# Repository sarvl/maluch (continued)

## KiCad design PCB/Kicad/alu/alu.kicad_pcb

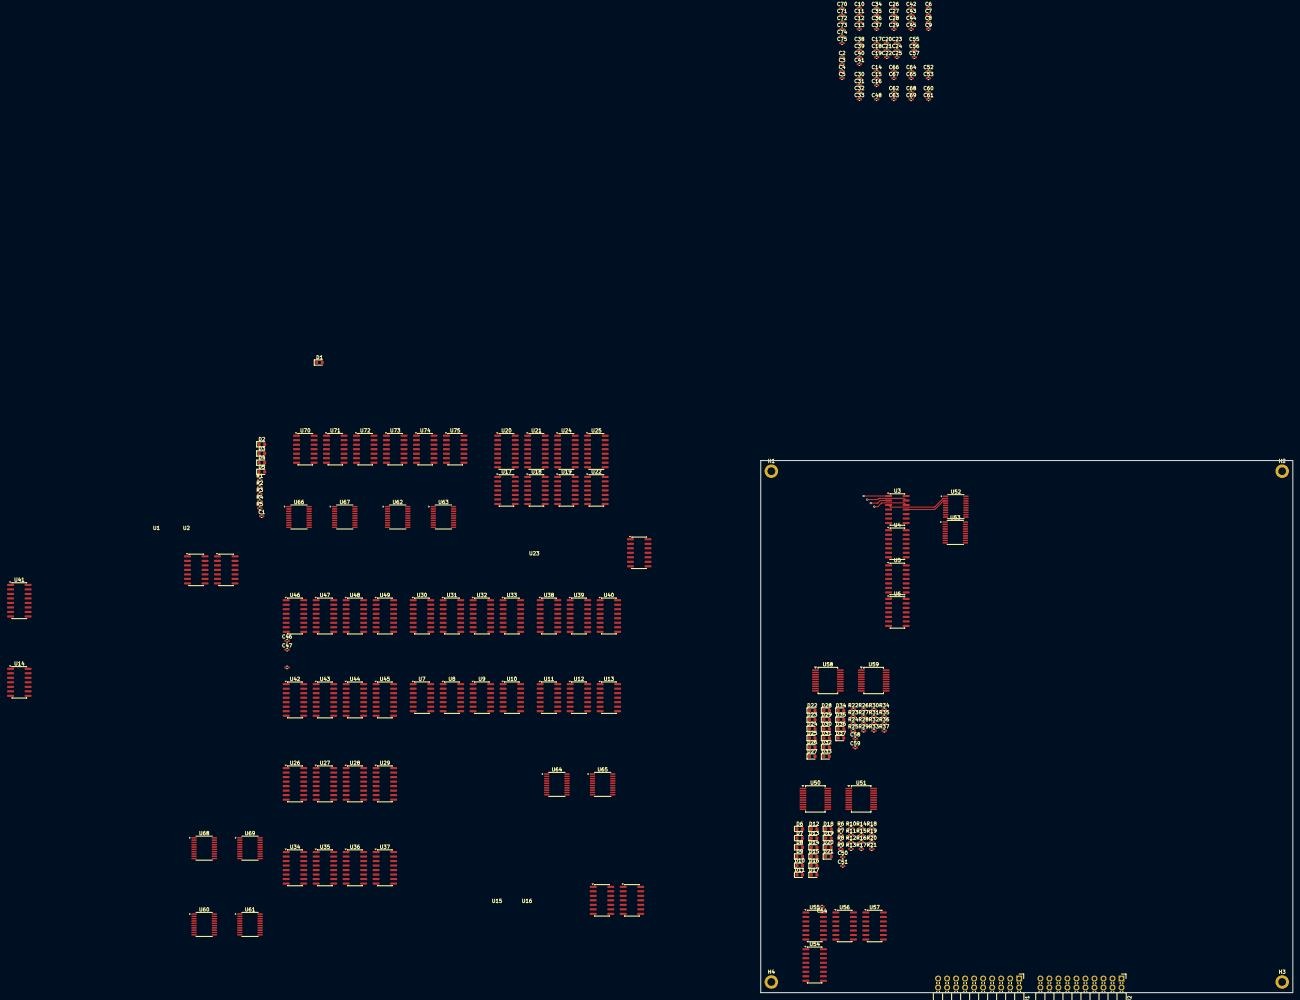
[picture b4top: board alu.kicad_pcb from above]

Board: 6 copper layers, 150.0 x 150.0 mm, 230 parts (0 on the bottom side), 335 nets.

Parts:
C1, C2, C3, C4, C5, C6, C7, C8, C9, C10, C11, C12, C13, C14, C15, C16, C17, C18, C19, C20, C21, C22, C23, C24, C25, C26, C27, C28, C29, C30, C31, C32, C33, C34, C35, C36, C37, C38, C39, C40, C41, C42, C43, C44, C45, C46, C47, C48, C49, C50, C51, C52, C53, C54, C55, C56, C57, C58, C59, C60, C61, C62, C63, C64, C65, C66, C67, C68, C69, C70, C71, C72, C73, C74, C75: 100nF; C_0402_1005Metric
D1: green; LED_0603_1608Metric
D2, D3, D4, D5: Yellow; LED_0603_1608Metric
D6, D7, D8, D9, D10, D11, D12, D13, D14, D15, D16, D17, D18, D19, D20, D21, D22, D23, D24, D25, D26, D27, D28, D29, D30, D31, D32, D33, D34, D35, D36, D37: red; LED_0603_1608Metric
H1, H2, H3, H4: MountingHole_Pad; MountingHole_2.2mm_M2_DIN965_Pad
J1, J2: out; PinHeader_2x10_P2.54mm_Horizontal
R1, R2, R3, R4, R5, R6, R7, R8, R9, R10, R11, R12, R13, R14, R15, R16, R17, R18, R19, R20, R21, R22, R23, R24, R25, R26, R27, R28, R29, R30, R31, R32, R33, R34, R35, R36, R37: 680; R_0402_1005Metric
U1, U7, U8, U9, U10, U75: 7408; SO-14_3.9x8.65mm_P1.27mm
U2, U15, U16, U73: 7404; SO-14_3.9x8.65mm_P1.27mm
U3, U4, U5, U6, U55, U56, U57, U70, U72, U74: 7432; SO-14_3.9x8.65mm_P1.27mm
U11, U12, U13, U14, U17, U18, U19, U22, U23, U71: 7486; SO-14_3.9x8.65mm_P1.27mm
U20, U21, U24, U25: 74283; SOIC-16_3.9x9.9mm_P1.27mm
U26, U27, U28, U29, U30, U31, U32, U33, U34, U35, U36, U37, U38, U39, U40, U41, U42, U43, U44, U45, U46, U47, U48, U49: 74257; SOIC-16_3.9x9.9mm_P1.27mm
U50, U51, U58, U59: 74377; SSOP-20_5.3x7.2mm_P0.65mm
U52, U53, U60, U61, U62, U63, U64, U65, U66, U67, U68, U69: 74245; TSSOP-20_4.4x6.5mm_P0.65mm
U54: 74139; SOIC-16_3.9x9.9mm_P1.27mm

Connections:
/ADD_SUB0: U20.4 (S1), U66.2 (A0)
/ADD_SUB1: U20.1 (S2), U66.3 (A1)
/ADD_SUB2: U20.13 (S3), U66.4 (A2)
/ADD_SUB3: U20.10 (S4), U66.5 (A3)
/ADD_SUB4: U21.4 (S1), U66.6 (A4)
/ADD_SUB5: U21.1 (S2), U66.7 (A5)
/ADD_SUB6: U21.13 (S3), U66.8 (A6)
/ADD_SUB7: U21.10 (S4), U66.9 (A7)
/ADD_SUB8: U24.4 (S1), U67.2 (A0)
/ADD_SUB9: U24.1 (S2), U67.3 (A1)
/ADD_SUB10: U24.13 (S3), U67.4 (A2)
/ADD_SUB11: U24.10 (S4), U67.5 (A3)
/ADD_SUB12: U25.4 (S1), U67.6 (A4)
/ADD_SUB13: U25.1 (S2), U67.7 (A5)
/ADD_SUB14: U25.13 (S3), U67.8 (A6)
/ADD_SUB15: U23.10, U25.10 (S4), U67.9 (A7)
/ADD_SUB/COUT0: U20.9 (C4), U21.7 (C0)
/ADD_SUB/COUT1: U21.9 (C4), U24.7 (C0)
/ADD_SUB/COUT2: U24.9 (C4), U25.7 (C0)
/AND0: U7.3, U60.2 (A0)
/AND1: U7.6, U60.3 (A1)
/AND2: U7.8, U60.4 (A2)
/AND3: U7.11, U60.5 (A3)
/AND4: U8.3, U60.6 (A4)
/AND5: U8.6, U60.7 (A5)
/AND6: U8.8, U60.8 (A6)
/AND7: U8.11, U60.9 (A7)
/AND8: U9.3, U61.2 (A0)
/AND9: U9.6, U61.3 (A1)
/AND10: U9.8, U61.4 (A2)
/AND11: U9.11, U61.5 (A3)
/AND12: U10.3, U61.6 (A4)
/AND13: U10.6, U61.7 (A5)
/AND14: U10.8, U61.8 (A6)
/AND15: U10.11, U61.9 (A7)
/A_BUS0: D6.2 (A), U3.1, U7.1, U11.1, U20.12 (A4), U21.12 (A4), U24.12 (A4), U25.12 (A4), U26.2 (I0a), U29.10 (I1d), U50.2 (Q0)
/A_BUS1: D8.2 (A), U3.13, U7.4, U11.4, U20.14 (A3), U21.14 (A3), U24.14 (A3), U25.14 (A3), U26.5 (I0b), U29.13 (I1c), U50.5 (Q1)
/A_BUS2: D10.2 (A), U3.9, U7.9, U11.9, U20.3 (A2), U21.3 (A2), U24.3 (A2), U25.3 (A2), U26.14 (I0c), U29.6 (I1b), U50.6 (Q2)
/A_BUS3: D12.2 (A), U3.4, U7.12, U11.12, U20.5 (A1), U21.5 (A1), U24.5 (A1), U25.5 (A1), U26.11 (I0d), U29.3 (I1a), U50.9 (Q3)
/A_BUS4: D14.2 (A), U4.1, U8.1, U12.1, U27.2 (I0a), U28.10 (I1d), U50.12 (Q4)
/A_BUS5: D16.2 (A), U4.4, U8.4, U12.4, U27.5 (I0b), U28.13 (I1c), U50.15 (Q5)
/A_BUS6: D18.2 (A), U4.9, U8.9, U12.9, U27.14 (I0c), U28.6 (I1b), U50.16 (Q6)
/A_BUS7: D20.2 (A), U4.12, U8.12, U12.12, U27.11 (I0d), U28.3 (I1a), U50.19 (Q7)
/A_BUS8: D7.2 (A), U5.1, U9.1, U13.1, U27.10 (I1d), U28.2 (I0a), U51.2 (Q0)
/A_BUS9: D9.2 (A), U5.4, U9.4, U13.4, U27.13 (I1c), U28.5 (I0b), U51.5 (Q1)
/A_BUS10: D11.2 (A), U5.9, U9.9, U13.9, U27.6 (I1b), U28.14 (I0c), U51.6 (Q2)
/A_BUS11: D13.2 (A), U5.12, U9.12, U13.12, U27.3 (I1a), U28.11 (I0d), U51.9 (Q3)
/A_BUS12: D15.2 (A), U6.1, U10.1, U14.1, U26.10 (I1d), U29.2 (I0a), U51.12 (Q4)
/A_BUS13: D17.2 (A), U6.4, U10.4, U14.4, U26.13 (I1c), U29.5 (I0b), U51.15 (Q5)
/A_BUS14: D19.2 (A), U6.9, U10.9, U14.9, U26.6 (I1b), U29.14 (I0c), U51.16 (Q6)
/A_BUS15: D21.2 (A), U6.12, U10.12, U14.12, U23.4, U23.9, U26.3 (I1a), U29.11 (I0d), U51.19 (Q7)
/B_BUS0: D22.2 (A), U2.5, U3.2, U7.2, U11.2, U18.2, U30.1 (S), U31.1 (S), U32.1 (S), U33.1 (S), U58.2 (Q0)
/B_BUS1: D24.2 (A), U2.9, U3.12, U7.5, U11.5, U17.5, U34.1 (S), U35.1 (S), U36.1 (S), U37.1 (S), U58.5 (Q1)
/B_BUS2: D26.2 (A), U3.10, U7.10, U11.10, U15.11, U17.10, U38.1 (S), U39.1 (S), U40.1 (S), U41.1 (S), U58.6 (Q2)
/B_BUS3: D28.2 (A), U3.5, U7.13, U11.13, U15.13, U17.13, U42.1 (S), U43.1 (S), U44.1 (S), U45.1 (S), U58.9 (Q3)
/B_BUS4: D30.2 (A), U2.1, U4.2, U8.2, U12.2, U19.2, U23.2, U58.12 (Q4)
/B_BUS5: D32.2 (A), U2.3, U4.5, U8.5, U12.5, U18.5, U22.5, U58.15 (Q5)
/B_BUS6: D34.2 (A), U4.10, U8.10, U12.10, U15.5, U18.10, U22.10, U58.16 (Q6)
/B_BUS7: D36.2 (A), U4.13, U8.13, U12.13, U15.9, U18.13, U22.13, U58.19 (Q7)
/B_BUS8: D23.2 (A), U5.2, U9.2, U13.2, U15.1, U22.2, U59.2 (Q0)
/B_BUS9: D25.2 (A), U5.5, U9.5, U13.5, U15.3, U19.5, U59.5 (Q1)
/B_BUS10: D27.2 (A), U5.10, U9.10, U13.10, U16.5, U19.10, U59.6 (Q2)
/B_BUS11: D29.2 (A), U5.13, U9.13, U13.13, U16.9, U19.13, U59.9 (Q3)
/B_BUS12: D31.2 (A), U6.2, U10.2, U14.2, U16.11, U59.12 (Q4)
/B_BUS13: D33.2 (A), U6.5, U10.5, U14.5, U16.13, U59.15 (Q5)
/B_BUS14: D35.2 (A), U6.10, U10.10, U14.10, U16.1, U59.16 (Q6)
/B_BUS15: D37.2 (A), U6.13, U10.13, U14.13, U16.3, U59.19 (Q7), U71.1
/CLK: J2.4, U50.11 (CP), U51.11 (CP), U58.11 (CP), U59.11 (CP)
/D0: J2.3, U50.3 (D0), U52.18 (B0), U58.3 (D0), U60.18 (B0), U62.18 (B0), U64.18 (B0), U66.18 (B0), U68.18 (B0), U70.1
/D1: J2.5, U50.4 (D1), U52.17 (B1), U58.4 (D1), U60.17 (B1), U62.17 (B1), U64.17 (B1), U66.17 (B1), U68.17 (B1), U70.2
/D2: J2.7, U50.7 (D2), U52.16 (B2), U58.7 (D2), U60.16 (B2), U62.16 (B2), U64.16 (B2), U66.16 (B2), U68.16 (B2), U72.1
/D3: J2.9, U50.8 (D3), U52.15 (B3), U58.8 (D3), U60.15 (B3), U62.15 (B3), U64.15 (B3), U66.15 (B3), U68.15 (B3), U72.2
/D4: J2.11, U50.13 (D4), U52.14 (B4), U58.13 (D4), U60.14 (B4), U62.14 (B4), U64.14 (B4), U66.14 (B4), U68.14 (B4), U70.4
/D5: J2.13, U50.14 (D5), U52.13 (B5), U58.14 (D5), U60.13 (B5), U62.13 (B5), U64.13 (B5), U66.13 (B5), U68.13 (B5), U70.5
/D6: J2.15, U50.17 (D6), U52.12 (B6), U58.17 (D6), U60.12 (B6), U62.12 (B6), U64.12 (B6), U66.12 (B6), U68.12 (B6), U72.4
/D7: J2.17, U50.18 (D7), U52.11 (B7), U58.18 (D7), U60.11 (B7), U62.11 (B7), U64.11 (B7), U66.11 (B7), U68.11 (B7), U72.5
/D8: J1.3, U51.3 (D0), U53.18 (B0), U59.3 (D0), U61.18 (B0), U63.18 (B0), U65.18 (B0), U67.18 (B0), U69.18 (B0), U70.9
/D9: J1.5, U51.4 (D1), U53.17 (B1), U59.4 (D1), U61.17 (B1), U63.17 (B1), U65.17 (B1), U67.17 (B1), U69.17 (B1), U70.10
/D10: J1.7, U51.7 (D2), U53.16 (B2), U59.7 (D2), U61.16 (B2), U63.16 (B2), U65.16 (B2), U67.16 (B2), U69.16 (B2), U72.9
/D11: J1.9, U51.8 (D3), U53.15 (B3), U59.8 (D3), U61.15 (B3), U63.15 (B3), U65.15 (B3), U67.15 (B3), U69.15 (B3), U72.10
/D12: J1.11, U51.13 (D4), U53.14 (B4), U59.13 (D4), U61.14 (B4), U63.14 (B4), U65.14 (B4), U67.14 (B4), U69.14 (B4), U70.12
/D13: J1.13, U51.14 (D5), U53.13 (B5), U59.14 (D5), U61.13 (B5), U63.13 (B5), U65.13 (B5), U67.13 (B5), U69.13 (B5), U70.13
/D14: J1.15, U51.17 (D6), U53.12 (B6), U59.17 (D6), U61.12 (B6), U63.12 (B6), U65.12 (B6), U67.12 (B6), U69.12 (B6), U72.12
/D15: J1.17, J2.18, R4.1, U51.18 (D7), U53.11 (B7), U59.18 (D7), U61.11 (B7), U63.11 (B7), U65.11 (B7), U67.11 (B7), U69.11 (B7), U72.13
/DECODE/~G_ARITH: U54.11 (O1), U56.2, U56.5
/DECODE/~G_CTRL: U54.9 (O3), U57.2, U57.5
/DECODE/~G_LOG: U54.12 (O0), U55.2, U55.5, U55.10, U55.13
/DECODE/~G_SHIFT: U54.10 (O2), U56.10, U56.13
/DECODE/~S0: U54.4 (O0), U55.1, U56.1, U56.9, U57.1
/DECODE/~S1: U54.5 (O1), U55.4, U56.4, U56.12, U57.4
/DECODE/~S2: U54.6 (O2), U55.9
/DECODE/~S3: U54.7 (O3), U55.12
/FC: J2.12, R5.1, U25.9 (C4)
/FO: J2.16, R2.1, U75.3
/FO_FZ/X0: U70.3, U74.1
/FO_FZ/X1: U70.6, U74.4
/FO_FZ/X2: U70.8, U74.9
/FO_FZ/X3: U70.11, U74.12
/FO_FZ/Y0: U72.3, U74.2
/FO_FZ/Y1: U72.6, U74.5
/FO_FZ/Y2: U72.8, U74.10
/FO_FZ/Y3: U72.11, U74.13
/FO_FZ/Z0: U73.4, U75.4
/FO_FZ/Z1: U73.6, U75.5
/FO_FZ/Z2: U73.8, U75.12
/FO_FZ/Z3: U73.10, U75.13
/FZ: J2.10, R3.1, U75.8
/IS_SUB: U2.10, U17.1, U17.4, U17.9, U17.12, U18.1, U18.4, U18.9, U18.12, U19.1, U19.4, U19.9, U19.12, U22.1, U22.4, U22.9, U22.12, U23.1, U71.2
/NOT0: U2.6, U64.2 (A0)
/NOT1: U2.8, U64.3 (A1)
/NOT2: U15.10, U64.4 (A2)
/NOT3: U15.12, U64.5 (A3)
/NOT4: U2.2, U64.6 (A4)
/NOT5: U2.4, U64.7 (A5)
/NOT6: U15.6, U64.8 (A6)
/NOT7: U15.8, U64.9 (A7)
/NOT8: U15.2, U65.2 (A0)
/NOT9: U15.4, U65.3 (A1)
/NOT10: U16.6, U65.4 (A2)
/NOT11: U16.8, U65.5 (A3)
/NOT12: U16.10, U65.6 (A4)
/NOT13: U16.12, U65.7 (A5)
/NOT14: U16.2, U65.8 (A6)
/NOT15: U16.4, U65.9 (A7)
/OP0: J1.4, U54.2 (A0)
/OP1: J1.8, U54.3 (A1)
/OP2: J1.14, U54.14 (A0)
/OP3: J1.18, U54.13 (A1)
/OR0: U3.3, U52.2 (A0)
/OR1: U3.11, U52.3 (A1)
/OR2: U3.8, U52.4 (A2)
/OR3: U3.6, U52.5 (A3)
/OR4: U4.3, U52.6 (A4)
/OR5: U4.6, U52.7 (A5)
/OR6: U4.8, U52.8 (A6)
/OR7: U4.11, U52.9 (A7)
/OR8: U5.3, U53.2 (A0)
/OR9: U5.6, U53.3 (A1)
/OR10: U5.8, U53.4 (A2)
/OR11: U5.11, U53.5 (A3)
/OR12: U6.3, U53.6 (A4)
/OR13: U6.6, U53.7 (A5)
/OR14: U6.8, U53.8 (A6)
/OR15: U6.11, U53.9 (A7)
/SHIFT0: U46.4 (Za), U68.2 (A0)
/SHIFT1: U46.7 (Zb), U68.3 (A1)
/SHIFT2: U46.12 (Zc), U68.4 (A2)
/SHIFT3: U46.9 (Zd), U68.5 (A3)
/SHIFT4: U47.4 (Za), U68.6 (A4)
/SHIFT5: U47.7 (Zb), U68.7 (A5)
/SHIFT6: U47.12 (Zc), U68.8 (A6)
/SHIFT7: U47.9 (Zd), U68.9 (A7)
/SHIFT8: U48.4 (Za), U69.2 (A0)
/SHIFT9: U48.7 (Zb), U69.3 (A1)
/SHIFT10: U48.12 (Zc), U69.4 (A2)
/SHIFT11: U48.9 (Zd), U69.5 (A3)
/SHIFT12: U49.4 (Za), U69.6 (A4)
/SHIFT13: U49.7 (Zb), U69.7 (A5)
/SHIFT14: U49.12 (Zc), U69.8 (A6)
/SHIFT15: U49.9 (Zd), U69.9 (A7)
/SHIFT_REG/LAYER1/Lout0: U30.4 (Za), U34.2 (I0a)
/SHIFT_REG/LAYER1/Lout1: U30.7 (Zb), U34.5 (I0b)
/SHIFT_REG/LAYER1/Lout2: U30.12 (Zc), U34.3 (I1a), U34.14 (I0c)
/SHIFT_REG/LAYER1/Lout3: U30.9 (Zd), U34.6 (I1b), U34.11 (I0d)
/SHIFT_REG/LAYER1/Lout4: U31.4 (Za), U34.13 (I1c), U35.2 (I0a)
/SHIFT_REG/LAYER1/Lout5: U31.7 (Zb), U34.10 (I1d), U35.5 (I0b)
/SHIFT_REG/LAYER1/Lout6: U31.12 (Zc), U35.3 (I1a), U35.14 (I0c)
/SHIFT_REG/LAYER1/Lout7: U31.9 (Zd), U35.6 (I1b), U35.11 (I0d)
/SHIFT_REG/LAYER1/Lout8: U32.4 (Za), U35.13 (I1c), U36.2 (I0a)
/SHIFT_REG/LAYER1/Lout9: U32.7 (Zb), U35.10 (I1d), U36.5 (I0b)
/SHIFT_REG/LAYER1/Lout10: U32.12 (Zc), U36.3 (I1a), U36.14 (I0c)
/SHIFT_REG/LAYER1/Lout11: U32.9 (Zd), U36.6 (I1b), U36.11 (I0d)
/SHIFT_REG/LAYER1/Lout12: U33.4 (Za), U36.13 (I1c), U37.2 (I0a)
/SHIFT_REG/LAYER1/Lout13: U33.7 (Zb), U36.10 (I1d), U37.5 (I0b)
/SHIFT_REG/LAYER1/Lout14: U33.12 (Zc), U37.3 (I1a), U37.14 (I0c)
/SHIFT_REG/LAYER1/Lout15: U33.9 (Zd), U37.6 (I1b), U37.11 (I0d)
/SHIFT_REG/LAYER1/R0: U26.4 (Za), U30.2 (I0a)
/SHIFT_REG/LAYER1/R1: U26.7 (Zb), U30.3 (I1a), U30.5 (I0b)
/SHIFT_REG/LAYER1/R2: U26.12 (Zc), U30.6 (I1b), U30.14 (I0c)
/SHIFT_REG/LAYER1/R3: U26.9 (Zd), U30.11 (I0d), U30.13 (I1c)
/SHIFT_REG/LAYER1/R4: U27.4 (Za), U30.10 (I1d), U31.2 (I0a)
/SHIFT_REG/LAYER1/R5: U27.7 (Zb), U31.3 (I1a), U31.5 (I0b)
/SHIFT_REG/LAYER1/R6: U27.12 (Zc), U31.6 (I1b), U31.14 (I0c)
/SHIFT_REG/LAYER1/R7: U27.9 (Zd), U31.11 (I0d), U31.13 (I1c)
/SHIFT_REG/LAYER1/R8: U28.4 (Za), U31.10 (I1d), U32.2 (I0a)
/SHIFT_REG/LAYER1/R9: U28.7 (Zb), U32.3 (I1a), U32.5 (I0b)
/SHIFT_REG/LAYER1/R10: U28.12 (Zc), U32.6 (I1b), U32.14 (I0c)
/SHIFT_REG/LAYER1/R11: U28.9 (Zd), U32.11 (I0d), U32.13 (I1c)
/SHIFT_REG/LAYER1/R12: U29.4 (Za), U32.10 (I1d), U33.2 (I0a)
/SHIFT_REG/LAYER1/R13: U29.7 (Zb), U33.3 (I1a), U33.5 (I0b)
/SHIFT_REG/LAYER1/R14: U29.12 (Zc), U33.6 (I1b), U33.14 (I0c)
/SHIFT_REG/LAYER1/R15: U29.9 (Zd), U33.11 (I0d), U33.13 (I1c)
/SHIFT_REG/LAYER2/Lout0: U34.4 (Za), U38.2 (I0a)
/SHIFT_REG/LAYER2/Lout1: U34.7 (Zb), U38.5 (I0b)
/SHIFT_REG/LAYER2/Lout2: U34.12 (Zc), U38.14 (I0c)
/SHIFT_REG/LAYER2/Lout3: U34.9 (Zd), U38.11 (I0d)
/SHIFT_REG/LAYER2/Lout4: U35.4 (Za), U38.3 (I1a), U39.2 (I0a)
/SHIFT_REG/LAYER2/Lout5: U35.7 (Zb), U38.6 (I1b), U39.5 (I0b)
/SHIFT_REG/LAYER2/Lout6: U35.12 (Zc), U38.13 (I1c), U39.14 (I0c)
/SHIFT_REG/LAYER2/Lout7: U35.9 (Zd), U38.10 (I1d), U39.11 (I0d)
/SHIFT_REG/LAYER2/Lout8: U36.4 (Za), U39.3 (I1a), U40.2 (I0a)
/SHIFT_REG/LAYER2/Lout9: U36.7 (Zb), U39.6 (I1b), U40.5 (I0b)
/SHIFT_REG/LAYER2/Lout10: U36.12 (Zc), U39.13 (I1c), U40.14 (I0c)
/SHIFT_REG/LAYER2/Lout11: U36.9 (Zd), U39.10 (I1d), U40.11 (I0d)
/SHIFT_REG/LAYER2/Lout12: U37.4 (Za), U40.3 (I1a), U41.2 (I0a)
/SHIFT_REG/LAYER2/Lout13: U37.7 (Zb), U40.6 (I1b), U41.5 (I0b)
/SHIFT_REG/LAYER2/Lout14: U37.12 (Zc), U40.13 (I1c), U41.14 (I0c)
/SHIFT_REG/LAYER2/Lout15: U37.9 (Zd), U40.10 (I1d), U41.11 (I0d)
/SHIFT_REG/LAYER3/Lout0: U38.4 (Za), U42.2 (I0a)
/SHIFT_REG/LAYER3/Lout1: U38.7 (Zb), U42.5 (I0b)
/SHIFT_REG/LAYER3/Lout2: U38.12 (Zc), U42.14 (I0c)
/SHIFT_REG/LAYER3/Lout3: U38.9 (Zd), U42.11 (I0d)
/SHIFT_REG/LAYER3/Lout4: U39.4 (Za), U43.2 (I0a)
/SHIFT_REG/LAYER3/Lout5: U39.7 (Zb), U43.5 (I0b)
/SHIFT_REG/LAYER3/Lout6: U39.12 (Zc), U43.14 (I0c)
/SHIFT_REG/LAYER3/Lout7: U39.9 (Zd), U43.11 (I0d)
/SHIFT_REG/LAYER3/Lout8: U40.4 (Za), U42.3 (I1a), U44.2 (I0a)
/SHIFT_REG/LAYER3/Lout9: U40.7 (Zb), U42.6 (I1b), U44.5 (I0b)
/SHIFT_REG/LAYER3/Lout10: U40.12 (Zc), U42.13 (I1c), U44.14 (I0c)
/SHIFT_REG/LAYER3/Lout11: U40.9 (Zd), U42.10 (I1d), U44.11 (I0d)
/SHIFT_REG/LAYER3/Lout12: U41.4 (Za), U43.3 (I1a), U45.2 (I0a)
/SHIFT_REG/LAYER3/Lout13: U41.7 (Zb), U43.6 (I1b), U45.5 (I0b)
/SHIFT_REG/LAYER3/Lout14: U41.12 (Zc), U43.13 (I1c), U45.14 (I0c)
/SHIFT_REG/LAYER3/Lout15: U41.9 (Zd), U43.10 (I1d), U45.11 (I0d)
/SHIFT_REG/LAYER4/Lout0: U42.4 (Za), U46.2 (I0a), U49.10 (I1d)
/SHIFT_REG/LAYER4/Lout1: U42.7 (Zb), U46.5 (I0b), U49.13 (I1c)
/SHIFT_REG/LAYER4/Lout2: U42.12 (Zc), U46.14 (I0c), U49.6 (I1b)
/SHIFT_REG/LAYER4/Lout3: U42.9 (Zd), U46.11 (I0d), U49.3 (I1a)
/SHIFT_REG/LAYER4/Lout4: U43.4 (Za), U47.2 (I0a), U48.10 (I1d)
/SHIFT_REG/LAYER4/Lout5: U43.7 (Zb), U47.5 (I0b), U48.13 (I1c)
/SHIFT_REG/LAYER4/Lout6: U43.12 (Zc), U47.14 (I0c), U48.6 (I1b)
/SHIFT_REG/LAYER4/Lout7: U43.9 (Zd), U47.11 (I0d), U48.3 (I1a)
/SHIFT_REG/LAYER4/Lout8: U44.4 (Za), U47.10 (I1d), U48.2 (I0a)
/SHIFT_REG/LAYER4/Lout9: U44.7 (Zb), U47.13 (I1c), U48.5 (I0b)
/SHIFT_REG/LAYER4/Lout10: U44.12 (Zc), U47.6 (I1b), U48.14 (I0c)
/SHIFT_REG/LAYER4/Lout11: U44.9 (Zd), U47.3 (I1a), U48.11 (I0d)
/SHIFT_REG/LAYER4/Lout12: U45.4 (Za), U46.10 (I1d), U49.2 (I0a)
/SHIFT_REG/LAYER4/Lout13: U45.7 (Zb), U46.13 (I1c), U49.5 (I0b)
/SHIFT_REG/LAYER4/Lout14: U45.12 (Zc), U46.6 (I1b), U49.14 (I0c)
/SHIFT_REG/LAYER4/Lout15: U45.9 (Zd), U46.3 (I1a), U49.11 (I0d)
/SHIFT_REG/REV: U2.12, U26.1 (S), U27.1 (S), U28.1 (S), U29.1 (S), U46.1 (S), U47.1 (S), U48.1 (S), U49.1 (S)
/XOR0: U11.3, U62.2 (A0)
/XOR1: U11.6, U62.3 (A1)
/XOR2: U11.8, U62.4 (A2)
/XOR3: U11.11, U62.5 (A3)
/XOR4: U12.3, U62.6 (A4)
/XOR5: U12.6, U62.7 (A5)
/XOR6: U12.8, U62.8 (A6)
/XOR7: U12.11, U62.9 (A7)
/XOR8: U13.3, U63.2 (A0)
/XOR9: U13.6, U63.3 (A1)
/XOR10: U13.8, U63.4 (A2)
/XOR11: U13.11, U63.5 (A3)
/XOR12: U14.3, U63.6 (A4)
/XOR13: U14.6, U63.7 (A5)
/XOR14: U14.8, U63.8 (A6)
/XOR15: U14.11, U63.9 (A7)
/~LOAD_A_REG: U50.1 (~E), U51.1 (~E), U57.3
/~LOAD_B_REG: U57.6, U58.1 (~E), U59.1 (~E)
/~SEL_ADD_SUB: U1.11, U66.19 (CE), U67.19 (CE)
/~SEL_ADD: U1.13, U56.3
/~SEL_AND: U55.6, U60.19 (CE), U61.19 (CE)
/~SEL_NOT: U55.11, U64.19 (CE), U65.19 (CE)
/~SEL_OR: U52.19 (CE), U53.19 (CE), U55.3
/~SEL_SHIFT: U1.8, U68.19 (CE), U69.19 (CE)
/~SEL_SHL: U1.9, U56.8
/~SEL_SHR: U1.10, U2.13, U56.11
/~SEL_SUB: U1.12, U2.11, U56.6
/~SEL_XOR: U55.8, U62.19 (CE), U63.19 (CE)
GND: C1.2, C2.2, C3.2, C4.2, C5.2, C6.2, C7.2, C8.2, C9.2, C10.2, C11.2, C12.2, C13.2, C14.2, C15.2, C16.2, C17.2, C18.2, C19.2, C20.2, C21.2, C22.2, C23.2, C24.2, C25.2, C26.2, C27.2, C28.2, C29.2, C30.2, C31.2, C32.2, C33.2, C34.2, C35.2, C36.2, C37.2, C38.2, C39.2, C40.2, C41.2, C42.2, C43.2, C44.2, C45.2, C46.2, C47.2, C48.2, C49.2, C50.2, C51.2, C52.2, C53.2, C54.2, C55.2, C56.2, C57.2, C58.2, C59.2, C60.2, C61.2, C62.2, C63.2, C64.2, C65.2, C66.2, C67.2, C68.2, C69.2, C70.2, C71.2, C72.2, C73.2, C74.2, C75.2, D1.1 (K), D2.1 (K), D3.1 (K), D4.1 (K), D5.1 (K), H1.1 (1_1), H2.1 (1_1), H3.1 (1_1), H4.1 (1_1), J1.2, J1.6, J1.10, J1.12, J1.16, J1.20, J2.2, J2.6, J2.8, J2.14, J2.20, R6.2, R7.2, R8.2, R9.2, R10.2, R11.2, R12.2, R13.2, R14.2, R15.2, R16.2, R17.2, R18.2, R19.2, R20.2, R21.2, R22.2, R23.2, R24.2, R25.2, R26.2, R27.2, R28.2, R29.2, R30.2, R31.2, R32.2, R33.2, R34.2, R35.2, R36.2, R37.2, U1.7 (GND), U2.7 (GND), U3.7 (GND), U4.7 (GND), U5.7 (GND), U6.7 (GND), U7.7 (GND), U8.7 (GND), U9.7 (GND), U10.7 (GND), U11.7 (GND), U12.7 (GND), U13.7 (GND), U14.7 (GND), U15.7 (GND), U16.7 (GND), U17.2, U17.7 (GND), U18.7 (GND), U19.7 (GND), U20.8 (GND), U21.8 (GND), U22.7 (GND), U23.7 (GND), U24.8 (GND), U25.8 (GND), U26.8 (GND), U26.15 (OE), U27.8 (GND), U27.15 (OE), U28.8 (GND), U28.15 (OE), U29.8 (GND), U29.15 (OE), U30.8 (GND), U30.15 (OE), U31.8 (GND), U31.15 (OE), U32.8 (GND), U32.15 (OE), U33.8 (GND), U33.10 (I1d), U33.15 (OE), U34.8 (GND), U34.15 (OE), U35.8 (GND), U35.15 (OE), U36.8 (GND), U36.15 (OE), U37.8 (GND), U37.10 (I1d), U37.13 (I1c), U37.15 (OE), U38.8 (GND), U38.15 (OE), U39.8 (GND), U39.15 (OE), U40.8 (GND), U40.15 (OE), U41.3 (I1a), U41.6 (I1b), U41.8 (GND), U41.10 (I1d), U41.13 (I1c), U41.15 (OE), U42.8 (GND), U42.15 (OE), U43.8 (GND), U43.15 (OE), U44.3 (I1a), U44.6 (I1b), U44.8 (GND), U44.10 (I1d), U44.13 (I1c), U44.15 (OE), U45.3 (I1a), U45.6 (I1b), U45.8 (GND), U45.10 (I1d), U45.13 (I1c), U45.15 (OE), U46.8 (GND), U46.15 (OE), U47.8 (GND), U47.15 (OE), U48.8 (GND), U48.15 (OE), U49.8 (GND), U49.15 (OE), U50.10 (GND), U51.10 (GND), U52.10 (GND), U53.10 (GND), U54.1 (E), U54.8 (GND), U54.15 (E), U55.7 (GND), U56.7 (GND), U57.7 (GND), U58.10 (GND), U59.10 (GND), U60.10 (GND), U61.10 (GND), U62.10 (GND), U63.10 (GND), U64.10 (GND), U65.10 (GND), U66.10 (GND), U67.10 (GND), U68.10 (GND), U69.10 (GND), U70.7 (GND), U71.7 (GND), U72.7 (GND), U73.7 (GND), U74.7 (GND), U75.7 (GND)
unnamed: D1.2 (A), R1.2
unnamed: D2.2 (A), R2.2
unnamed: D3.2 (A), R3.2
unnamed: D4.2 (A), R4.2
unnamed: D5.2 (A), R5.2
unnamed: D6.1 (K), R6.1
unnamed: D7.1 (K), R7.1
unnamed: D8.1 (K), R8.1
unnamed: D9.1 (K), R9.1
unnamed: D10.1 (K), R10.1
unnamed: D11.1 (K), R11.1
unnamed: D12.1 (K), R12.1
unnamed: D13.1 (K), R13.1
unnamed: D14.1 (K), R14.1
unnamed: D15.1 (K), R15.1
unnamed: D16.1 (K), R16.1
unnamed: D17.1 (K), R17.1
unnamed: D18.1 (K), R18.1
unnamed: D19.1 (K), R19.1
unnamed: D20.1 (K), R20.1
unnamed: D21.1 (K), R21.1
unnamed: D22.1 (K), R22.1
unnamed: D23.1 (K), R23.1
unnamed: D24.1 (K), R24.1
unnamed: D25.1 (K), R25.1
unnamed: D26.1 (K), R26.1
unnamed: D27.1 (K), R27.1
unnamed: D28.1 (K), R28.1
unnamed: D29.1 (K), R29.1
unnamed: D30.1 (K), R30.1
unnamed: D31.1 (K), R31.1
unnamed: D32.1 (K), R32.1
unnamed: D33.1 (K), R33.1
unnamed: D34.1 (K), R34.1
unnamed: D35.1 (K), R35.1
unnamed: D36.1 (K), R36.1
unnamed: D37.1 (K), R37.1
unnamed: U18.3, U20.6 (B1)
unnamed: U17.6, U20.2 (B2)
unnamed: U17.8, U20.15 (B3)
unnamed: U17.11, U20.11 (B4)
unnamed: U17.3, U20.7 (C0)
unnamed: U19.3, U21.6 (B1)
unnamed: U18.6, U21.2 (B2)
unnamed: U18.8, U21.15 (B3)
unnamed: U18.11, U21.11 (B4)
unnamed: U23.5, U71.3
unnamed: U23.6, U73.1
unnamed: U23.8, U75.2
unnamed: U22.3, U24.6 (B1)
unnamed: U19.6, U24.2 (B2)
unnamed: U19.8, U24.15 (B3)
unnamed: U19.11, U24.11 (B4)
unnamed: U23.3, U25.6 (B1)
unnamed: U22.6, U25.2 (B2)
unnamed: U22.8, U25.15 (B3)
unnamed: U22.11, U25.11 (B4)
unnamed: U73.2, U75.1
unnamed: U73.3, U74.3
unnamed: U73.5, U74.6
unnamed: U73.9, U74.8
unnamed: U73.11, U74.11
unnamed: U75.6, U75.9
unnamed: U75.10, U75.11
VCC: C1.1, C2.1, C3.1, C4.1, C5.1, C6.1, C7.1, C8.1, C9.1, C10.1, C11.1, C12.1, C13.1, C14.1, C15.1, C16.1, C17.1, C18.1, C19.1, C20.1, C21.1, C22.1, C23.1, C24.1, C25.1, C26.1, C27.1, C28.1, C29.1, C30.1, C31.1, C32.1, C33.1, C34.1, C35.1, C36.1, C37.1, C38.1, C39.1, C40.1, C41.1, C42.1, C43.1, C44.1, C45.1, C46.1, C47.1, C48.1, C49.1, C50.1, C51.1, C52.1, C53.1, C54.1, C55.1, C56.1, C57.1, C58.1, C59.1, C60.1, C61.1, C62.1, C63.1, C64.1, C65.1, C66.1, C67.1, C68.1, C69.1, C70.1, C71.1, C72.1, C73.1, C74.1, C75.1, J1.1, J1.19, J2.1, J2.19, R1.1, U1.14 (VCC), U2.14 (VCC), U3.14 (VCC), U4.14 (VCC), U5.14 (VCC), U6.14 (VCC), U7.14 (VCC), U8.14 (VCC), U9.14 (VCC), U10.14 (VCC), U11.14 (VCC), U12.14 (VCC), U13.14 (VCC), U14.14 (VCC), U15.14 (VCC), U16.14 (VCC), U17.14 (VCC), U18.14 (VCC), U19.14 (VCC), U20.16 (VCC), U21.16 (VCC), U22.14 (VCC), U23.12, U23.13, U23.14 (VCC), U24.16 (VCC), U25.16 (VCC), U26.16 (VCC), U27.16 (VCC), U28.16 (VCC), U29.16 (VCC), U30.16 (VCC), U31.16 (VCC), U32.16 (VCC), U33.16 (VCC), U34.16 (VCC), U35.16 (VCC), U36.16 (VCC), U37.16 (VCC), U38.16 (VCC), U39.16 (VCC), U40.16 (VCC), U41.16 (VCC), U42.16 (VCC), U43.16 (VCC), U44.16 (VCC), U45.16 (VCC), U46.16 (VCC), U47.16 (VCC), U48.16 (VCC), U49.16 (VCC), U50.20 (VCC), U51.20 (VCC), U52.1 (A->B), U52.20 (VCC), U53.1 (A->B), U53.20 (VCC), U54.16 (VCC), U55.14 (VCC), U56.14 (VCC), U57.9, U57.10, U57.12, U57.13, U57.14 (VCC), U58.20 (VCC), U59.20 (VCC), U60.1 (A->B), U60.20 (VCC), U61.1 (A->B), U61.20 (VCC), U62.1 (A->B), U62.20 (VCC), U63.1 (A->B), U63.20 (VCC), U64.1 (A->B), U64.20 (VCC), U65.1 (A->B), U65.20 (VCC), U66.1 (A->B), U66.20 (VCC), U67.1 (A->B), U67.20 (VCC), U68.1 (A->B), U68.20 (VCC), U69.1 (A->B), U69.20 (VCC), U70.14 (VCC), U71.14 (VCC), U72.14 (VCC), U73.13, U73.14 (VCC), U74.14 (VCC), U75.14 (VCC)

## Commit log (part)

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2025-07-11 init
2025-07-11 docs
    test
2025-07-11 basic assembler ; simulator WIP
2025-07-15 isa overhaul
2025-07-16 io draft
2025-07-16 migrate simulator to /Soft
2025-07-16 add gitignore to rtl impl
2025-07-16 init rtl implementation
2025-07-16 create alu module
2025-07-17 added a tree reorganization from branch
2025-07-17 isa bugfix ; adjusted assembler NOT TESTED
2025-07-17 assembler bugfixes ; test framework ; tests
2025-07-17 add csr to alu
2025-07-17 add vcd dump to alu_tb
2025-07-17 script for compiling and simulating
2025-07-18 migrate to .fst waveforms
2025-07-19 Simulator first version - no IO yet ; assembler bugfix ; isa bugfix
2025-07-20 simulator IO support ; assembler bugfixes ; isa bugfixes
2025-07-26 simulator overhaul - barebones commandline
2025-07-30 basic core working
2025-08-03 tool update ; simulator overhaul
2025-08-03 skipped a file
2025-08-06 refactor for working branching
2025-08-11 add preprocesor optimization for importing modules
2025-08-11 create precision simulation and add basic test for counter
2025-09-09 migrate core interface to core_i
2025-09-09 add decoder testbench
2025-09-09 Optimize top testbench
2025-09-09 Memory core functionality
2025-09-11 Change mem bus to 32b
2025-09-27 Added vga_controller.sv file
2025-09-29 memory controller
2025-10-01 Exchanged bus interface with normal conections
2025-10-01 alu behavioral model
2025-10-02 Added working graphics card module
2025-10-02 Added working graphics card
2025-10-02 Added graphics_card testbench and char_rom memory
2025-10-03 Added missing logic from interface
2025-10-04 isa update
2025-10-06 Minor fixed, mainly directory path strings
2025-10-07 bugfix: source
2025-10-07 implementation of most features, lacks interrupts
2025-10-08 remove core_i file
2025-10-08 refactor alu
2025-10-08 fix reset error
2025-10-08 add makefile for verilator
2025-10-10 QoL stuff ; show command
2025-10-10 forgot makefile ; fixed simulator bug
2025-10-10 unless bugs are found, finished interrupt design
2025-10-12 removed hlt
2025-10-12 Code changes
2025-10-12 bugfix
2025-10-12 Revert "Code changes"
    This reverts commit a699a3ead8c12b348adec7c25efd6674342bfa04.
2025-10-12 changed interrupt mechanism
2025-10-12 support for new int mechanism
2025-10-12 create lib for pcbs
2025-10-12 create kicad project template
2025-10-13 update testbenches
2025-10-13 fix verilator linting error
2025-10-13 updated design document
2025-10-13 removed unnecessary connections
2025-10-13 Added trial2png file for testbenching and corrected gpu data output
2025-10-15 bugfixes ; stylistic changes
2025-10-15 update regfile
2025-10-15 IO drafts
2025-10-17 Deleted single pixel coloring
2025-10-17 Changed vram_address length
2025-10-17 add pcb constraints
2025-10-17 Revert "Merge branch 'pcb' of https://github.com/sarvl/maluch into pcb"
    This reverts commit 8762465c96191b8baaf434daf7fd6a710192f053, reversing
    changes made to c228ab879154aae27a8ab371f1c6d3d83fea3cab.
2025-10-17 Reapply "Merge branch 'pcb' of https://github.com/sarvl/maluch into pcb"
    This reverts commit 931a64993b22d8fa83f97669744d0938aaa1e416.
2025-10-17 interrupt bug fix
2025-10-17 started 74xx implementation; added ALU
2025-10-20 implemented control unit using mostly 74xx chips
2025-10-23 Added keyboard controller
2025-10-25 mem_ctr_74xx_v1
2026-04-22 routed control signals
2026-04-24 bus start
2026-04-26 bus in progress
2026-05-02 Add decoder IN/OUT instructions testbench
2026-05-02 Add PUSH instruction test to control_unit_tb
2026-05-02 Add stack pointer and register_file testbench
2026-05-02 Add support for IN and OUT instructions to the decoder
2026-05-02 Rename decoder to control_unit
2026-05-02 Modified register_file to support paraller writing to Rd and SP
2026-05-02 Fixed nameing in ps2_keyboard_controller
2026-05-02 Added ps2 keyboard controller tb
2026-05-02 Updated testbench
2026-05-02 Refactoring ps2 keyboard controller
2026-05-02 Add support for PUSH instruction
2026-05-02 Adapt counter to updated design assumptions
2026-05-02 Add signal to control csr
2026-05-02 Add PULL instruction test to control_unit_tb
2026-05-02 Changed name of the file to the proper one
2026-05-02 Add LDW/STW instruction tests to decoder_tb
2026-05-02 Add REG_SP parameter
2026-05-02 Change _reset to active-low in register_file
2026-05-02 Add failed tests counter to decoder_tb
2026-05-02 Added io_w_en signal and separation of combinational logic of outputs
2026-05-02 Add memory controller driver, with LDW/STW instruction support
2026-05-02 Added debouncer
2026-05-02 One reset at beginning, and IN condition fix
2026-05-02 Move outcome_driver logic into register_driver
2026-05-02 Add support for PULL instruction
2026-05-02 Reformat ports in decoder
2026-05-02 Refactore decoder
2026-05-02 Add support for branch instructions
2026-05-02 Add RET instruction test to control_unit_tb
2026-05-02 Update core_tb program to test interrupts
2026-05-02 initial testing of external IP
2026-05-02 Fix wrong reset polarity in register_file
2026-05-02 Fix wrong clock pulse width and tfp flush bug in core_tb
2026-05-02 add .gitignore for vivado
2026-05-02 Timer io pins renamed, added busy flag
2026-05-02 Memory_controller + Memory almost done. Backup if fail later
2026-05-02 Fix fatal flaw - partialy checking register driver in some tests in control_unit_tb
2026-05-02 Fix CALL/RET instruction test condition in program_counter_tb
2026-05-02 Code cleanup in control_unit_tb
2026-05-02 Fix programmer FSM logic
2026-05-02 Adapt core_tb to updated design assumptions
2026-05-02 Add function to handle insctructions read
2026-05-02 Fix program_counter_tb, wrong immediate testing
2026-05-02 Update instruction encoder in control_unit_tb
2026-05-02 Code refactore in control_unit
2026-05-02 Add RET instruction test to program_counter_tb
2026-05-02 Fix fatal flaw - wrongly handled OUT/STW/PUSH in control_unit
2026-05-02 Add GPU/VGA modules and tests
2026-05-02 Add IN/OUT basic handling in core_tb
2026-05-02 Driving kclk inout
2026-05-02 Example code to test some basic instructions
2026-05-02 IO changes
2026-05-02 Add io_bridge_tb
2026-05-02 Update instruction tests, now testing immediate too
2026-05-02 Add support for CALL instruction in program_counter
2026-05-02 Add CMP/TEST/reserved instructions test to control_unit_tb
2026-05-02 Add io_bridge module
2026-05-02 Finish memory controller
2026-05-02 Update example code to test more instructions
2026-05-02 Rename module to program_counter
2026-05-02 Code refactore and memory handling in core_tb
2026-05-02 Memory controller tb done TODO adjust after mem_ctr changes
2026-05-02 PUSH instruction code refactore
2026-05-02 Add instruction encoder in program_counter_tb
2026-05-02 Add CALL instruction test to program_counter_tb
2026-05-02 Add support for MOV instruction
2026-05-02 Fix some drivers not handling immediate
2026-05-02 Delate PROCESSING state to omit problem with frames reception; Make some code refactor
2026-05-02 Update test program for core_tb
2026-05-02 Code refactore in program_counter_tb
2026-05-02 Memory tb done, TODO change after memory update
2026-05-02 Added memory controller
2026-05-02 Added sim_precise.sh
2026-05-02 Adapt core module and submodules, to support interrupts
2026-05-02 Adapt ps2_keyboard_controller_tb
2026-05-02 Update ports name to match documentation
2026-05-02 Add support for RET instruction in program_counter
2026-05-02 Changed to Harvard architecture, TODO change data to 16b
2026-05-02 Add functions to handle data read/write
2026-05-02 Update module interconnections in core
2026-05-02 Change std::vector to std::array in progmem
2026-05-02 Update core_tb to support basic interrupt testing
2026-05-02 Add support for CALL instruction in control_unit
2026-05-02 Fix mistake that blocked simulation build
2026-05-02 Add branch instructions test to control_unit_tb
2026-05-02 Fix invalid opcode affecting instruction pointer
2026-05-02 Memory controller + Memory Done. Data path updated
2026-05-02 Adapted memory
2026-05-02 Add interrupt_controller_tb
2026-05-02 Memory controller done, TODO change data to 16b
2026-05-02 Code cleanup and refactore
2026-05-02 Port counter testbench to Verilator C++
2026-05-02 Small Hotfix. Memory + Controller Done
2026-05-02 Add CALL instruction test to control_unit_tb
2026-05-02 Adapt ports nameing in core, and update them in core_tb
2026-05-02 Add MOV instruction test to control_unit_tb
2026-05-02 Add interrupt_controller
2026-05-02 Update core_tb to simulate instruction fetch delay and memory write delay
2026-05-02 Fix in program_counter, not handling immediate
2026-05-02 Add support for RET instruction in control_unit
2026-05-02 Enable inout support
2026-05-02 Add support for kclk inout
2026-05-02 Add support for CMP/TEST instructions with reserved functs
2026-05-04 continuing bus routing
2026-05-06 routed signals and buses
2026-05-06 drc ok, no silkscreen
2026-05-06 silkscreen ok
2026-05-08 decoupling C RAM ROM
2026-05-22 routes
2026-05-27 mess
2026-05-30 control unit logic routing done
2026-05-31 początek łączenia decapów
2026-06-01 added fasmg proof of concept
2026-06-01 make simulator read binary files
2026-06-01 Added string support for db
2026-06-01 Ported all mnemonic macros to CALM instructions
2026-06-01 remove old assembler stuff
2026-06-01 Io docs (#16)
    * IO documentation
2026-06-01 Author update
2026-06-01 Added mov instruction
2026-06-01 Add compontents for power
2026-06-01 rename board to timer
2026-06-01 Added proper labels
2026-06-01 fix typo in timer docs
2026-06-01 added a rudimentary disassembler
2026-06-01 overwritten `db` and `dw` directives
2026-06-01 swapped stw arguments (its correct now)
2026-06-01 swap argument order in `in` opcode
    now it follows the dst, src convention
2026-06-01 change the assembly test tooling to use the new assembler
2026-06-01 implemented all the dyadic (binary) opcodes
2026-06-01 fix documentation
2026-06-01 implemented all the niladic (nullary) opcodes
2026-06-01 removed unused `file.cpp` and `file.h`
2026-06-01 fix disassembler
2026-06-01 Ported os_test.cpp to the new assembler
2026-06-01 ported all the examples to assembly
2026-06-01 moved `test` out of the dyadic loop as it doesnt modify anything
2026-06-01 ported g00t00 and g00t01 to the new assembler
2026-06-01 add gpu types
2026-06-01 implemented all monadic (unary) functions
2026-06-05 board size + ground vias
2026-06-05 visual fix
2026-06-08 Modify alu logic for variable shift
2026-06-08 Nexys4DDR FPGA implementation
2026-06-08 small fixes to os_test
2026-06-08 Add code uploading script
2026-06-08 Add default boot program & tetris
2026-06-13 silkscreen done
2026-06-13 silkscreen fix
2026-06-27 spaghetti
